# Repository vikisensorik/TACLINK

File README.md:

# TACLINK

> **A PIC32-based interface board for reading and routing 36-sensor tactile array data via I²C and SPI.**

**TACLINK** is an interface controller board designed to read and process tactile sensor data from a dedicated 36-sensor high-density tactile module *(currently under development)*. Powered by the PIC32MM0256GPM036 microcontroller in a UQFN-40 package, TACLINK is built to sample, manage, and route data from dense tactile arrays. It offers flexible communication options, utilizing I²C, Hardware SPI (HW SPI), and Software SPI (SW SPI) protocols.

## Features

- **Core Processing:** PIC32MM0256GPM036 microcontroller (UQFN-40 package)
- **High-Density Interfacing:** Designed to manage data from a 36-sensor tactile array
- **Dual-SPI Architecture:**
  - **Software SPI (SW SPI):** Dedicated to reading raw data from the upstream tactile sensor module.
  - **Hardware SPI (HW SPI):** High-speed data transmission to downstream external host systems.
- **Additional Protocols:** I²C support for expanded peripheral communication.
- **Target Applications:** Robotics, touch-sensitive interfaces, and pressure-mapping systems.

## Project Structure

```
taclink/
├── README.md
├── LICENSE
├── electronics/                    # Hardware design files
│   ├── schematic/                  # Circuit schematics (.sch)
│   ├── pcb/                        # Board layout (.brd)
│   ├── libraries/                  # Custom Eagle symbols and footprints (.lbr)
│   └── manufacturing/              # Production files
│       ├── gerbers/                # Gerber files for PCB fabrication
│       ├── BOM.csv                 # Bill of Materials
│       └── pick_and_place.csv      # Component placement file
├── firmware/                       # PIC32 source code
├── cad/                            # 3D models and enclosure files
│   ├── enclosure/                  # Case/housing STEP/STL files
│   └── assembly/                   # Assembly models
└── documents/                      # Documentation
    ├── datasheets/                 # Component datasheets
    ├── pinout/                     # Pin mapping diagrams
    └── guides/                     # User guides and application notes
```

## Use Case

TACLINK acts as the critical bridge between a high-density tactile sensing module (featuring 36 pressure sensors) and a host system. It communicates with the upstream sensor module using a Software SPI (SW SPI) protocol to continuously sample detailed pressure data. 

Designed for applications such as robotics, haptic interfaces, and pressure-mapping systems, TACLINK runs optimized firmware to acquire, process, and format the raw sensor readings. It then transmits this structured tactile data to an external system (such as a connected computer, robot controller, or external MCU) via a fast Hardware SPI (HW SPI) connection.

## Board Images

**Populated Module**  

**Board Layout**  

**Schematics**  

## Additional Details

- **Pin headers** are provided for programming the MCU and interfacing with external sensors and components.  
- **Low-power operation** and compact form factor make it ideal for embedded systems and portable tactile solutions.  
- Firmware development and sensor interfacing can be customized based on specific application needs.

---

## Usage, Attribution, and Licensing

This project is provided for **personal, academic, and research purposes only**. 

⛔ **Commercial use is strictly prohibited.** You may not use, modify, or build upon this design for any commercial or for-profit purpose without explicit prior written permission from the author.

If you use or adapt any part of this work for academic or research purposes, **you must credit the original author**:

**Vignesh Natarajan (Viki)**  
🌐 [vikisensorik.com](https://vikisensorik.com)

This project is licensed under the **Creative Commons Attribution-NonCommercial 4.0 International License (CC BY-NC 4.0)**.  
To view a copy of this license, visit: [https://creativecommons.org/licenses/by-nc/4.0/](https://creativecommons.org/licenses/by-nc/4.0/)

### Academic Citation
If you use this design or reference this work in academic research, publications, or theses, please cite this repository using the following BibTeX entry:

```bibtex
@misc{vnatarajan_taclink,
  author       = {Vignesh Natarajan (Viki)},
  title        = {TACLINK: A High-Density Tactile Controller Module},
  year         = {2025},
  howpublished = {\url{https://github.com/vikisensorik/taclink} and \url{https://vikisensorik.com}},
  note         = {Accessed: 2025-04-11}
}

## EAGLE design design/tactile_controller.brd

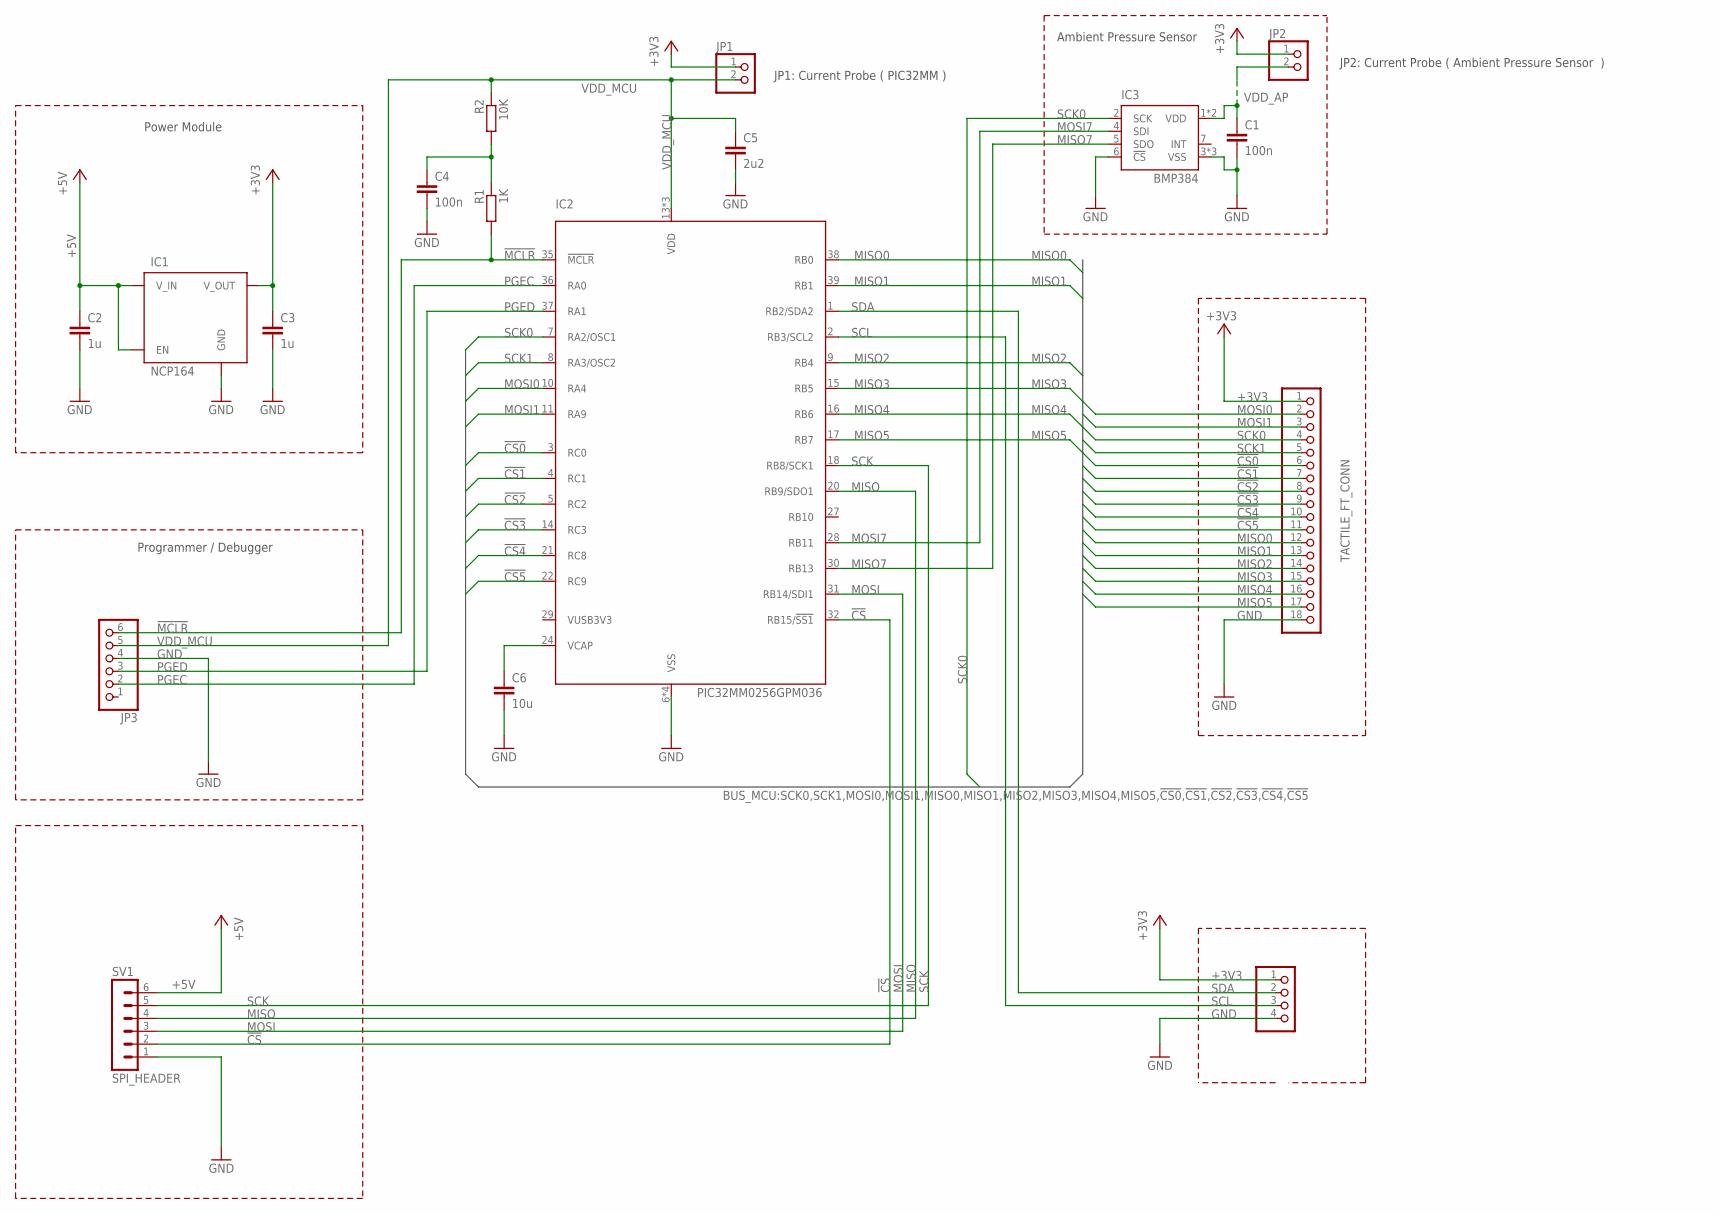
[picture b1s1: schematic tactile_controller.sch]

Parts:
ACTIVE_NAIL_CONN: PINHD-1X4/90; 1X04/90
C1: 100n; C0402
C2, C3: 1u; C0402
C4: 100n; C0603
C5: 2u2; C0402
C6: 10u; C0402
IC1: NCP164; NCP164_3.3V_REGULATOR_TSOP5
IC2: PIC32MM0256GPM036; PIC32MM0256GPM036_UQFN_40PIN
IC3: BMP384
JP1, JP2: 1X02
JP3: PINHD-1X6/90; 1X06/90
R1: 1K; R0603
R2: 10K; R0603
SV1: SPI_HEADER; MA06-1
TACTILE_FT_CONN: PINHD-1X18/90; 1X18/90

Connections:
!CS: IC2.32 (RB15/!SS1), SV1.2
!CS0: IC2.3 (RC0), TACTILE_FT_CONN.6
!CS1: IC2.4 (RC1), TACTILE_FT_CONN.7
!CS2: IC2.5 (RC2), TACTILE_FT_CONN.8
!CS3: IC2.14 (RC3), TACTILE_FT_CONN.9
!CS4: IC2.21 (RC8), TACTILE_FT_CONN.10
!CS5: IC2.22 (RC9), TACTILE_FT_CONN.11
!MCLR: IC2.35 (!MCLR), JP3.6, R1.2
+3V3: ACTIVE_NAIL_CONN.1, C3.1, IC1.5 (V_OUT), JP1.1, JP2.1, TACTILE_FT_CONN.1
+5V: C2.1, IC1.1 (V_IN), IC1.3 (EN), SV1.6
GND: ACTIVE_NAIL_CONN.4, C1.2, C2.2, C3.2, C4.2, C5.2, C6.2, IC1.2 (GND), IC2.6 (VSS), IC2.12 (VSS), IC2.33 (VSS), IC2.41 (VSS), IC3.3 (VSS), IC3.6 (!CS), IC3.8 (VSS), IC3.9 (VSS), JP3.4, SV1.1, TACTILE_FT_CONN.18
MISO: IC2.20 (RB9/SDO1), SV1.4
MISO0: IC2.38 (RB0), TACTILE_FT_CONN.12
MISO1: IC2.39 (RB1), TACTILE_FT_CONN.13
MISO2: IC2.9 (RB4), TACTILE_FT_CONN.14
MISO3: IC2.15 (RB5), TACTILE_FT_CONN.15
MISO4: IC2.16 (RB6), TACTILE_FT_CONN.16
MISO5: IC2.17 (RB7), TACTILE_FT_CONN.17
MISO7: IC2.30 (RB13), IC3.5 (SDO)
MOSI: IC2.31 (RB14/SDI1), SV1.3
MOSI0: IC2.10 (RA4), TACTILE_FT_CONN.2
MOSI1: IC2.11 (RA9), TACTILE_FT_CONN.3
MOSI7: IC2.28 (RB11), IC3.4 (SDI)
unnamed: C4.1, R1.1, R2.2
unnamed: C6.1, IC2.24 (VCAP)
PGEC: IC2.36 (RA0), JP3.2
PGED: IC2.37 (RA1), JP3.3
SCK: IC2.18 (RB8/SCK1), SV1.5
SCK0: IC2.7 (RA2/OSC1), IC3.2 (SCK), TACTILE_FT_CONN.4
SCK1: IC2.8 (RA3/OSC2), TACTILE_FT_CONN.5
SCL: ACTIVE_NAIL_CONN.3, IC2.2 (RB3/SCL2)
SDA: ACTIVE_NAIL_CONN.2, IC2.1 (RB2/SDA2)
VDD_AP: C1.1, IC3.1 (VDD), IC3.10 (VDD), JP2.2
VDD_MCU: C5.1, IC2.13 (VDD), IC2.26 (VDD), IC2.34 (VDD), JP1.2, JP3.5, R2.1

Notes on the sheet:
Power Module
Programmer / Debugger
Ambient Pressure Sensor
JP1: Current Probe ( PIC32MM )
JP2: Current Probe ( Ambient Pressure Sensor )

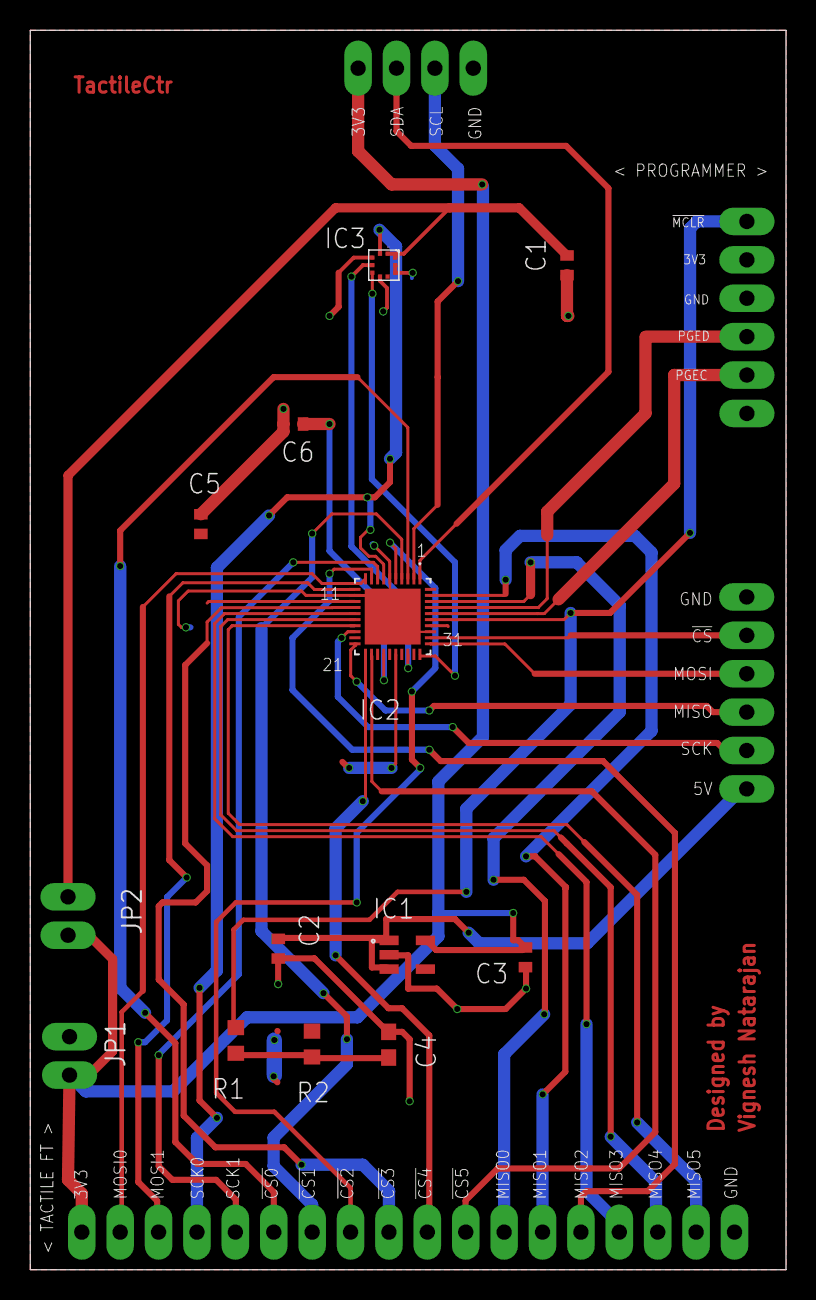
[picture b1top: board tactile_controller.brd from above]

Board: 2 copper layers, 50.0 x 82.0 mm, 17 parts (0 on the bottom side), 34 nets.

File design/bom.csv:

Part,Value,Device,Quantity
ACTIVE_NAIL_CONN,,PINHD-1X4/90,1
C1,100n,C-EUC0402,1
C2,1u,C-EUC0402,2
C4,1u,C-EUC0603,1
C5,2u2,C-EUC0402,1
C6,10u,C-EUC0402,1
IC1,NCP164,NCP164_3.3V_REGULATOR,1
IC2,PIC32MM0256GPM036,"PIC32MM"";""PIC32MM0256GPM036_UQFN_40PIN",1
IC3,BMP384,BMP384,1
JP1, ,PINHD-1X2,1
JP2, ,PINHD-1X2,1
R1,1K,R-EU_R0603,1
R2,10K,R-EU_R0603,1
SV1,SPI_HEADER,MA06-1,1
SV2,53261-05,53261-05,1
TACTILE_FT_CONN,,PINHD-1X18/90,1
